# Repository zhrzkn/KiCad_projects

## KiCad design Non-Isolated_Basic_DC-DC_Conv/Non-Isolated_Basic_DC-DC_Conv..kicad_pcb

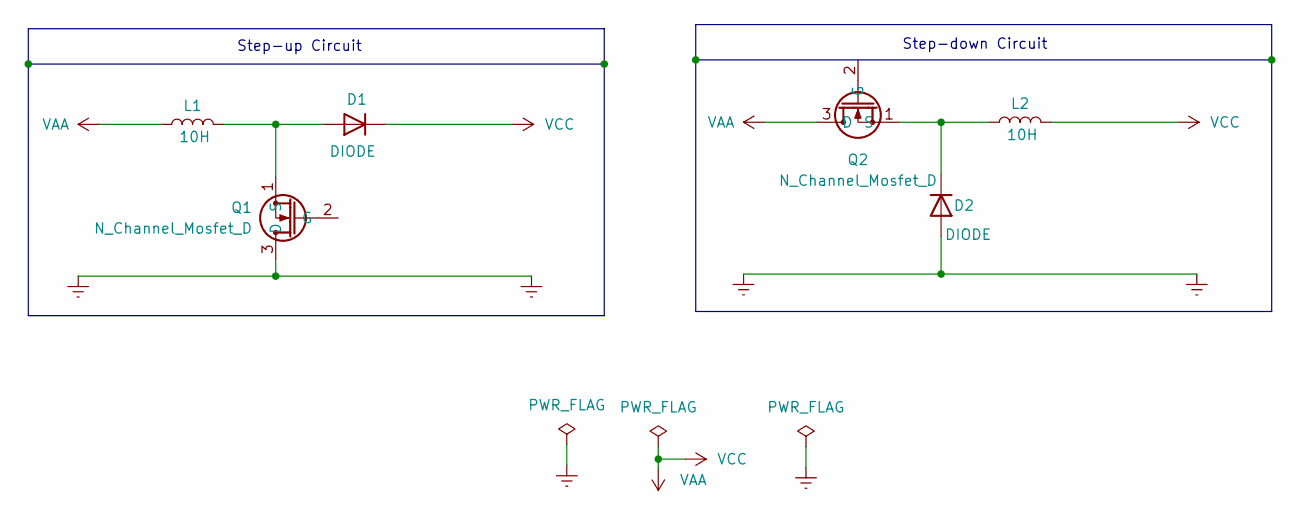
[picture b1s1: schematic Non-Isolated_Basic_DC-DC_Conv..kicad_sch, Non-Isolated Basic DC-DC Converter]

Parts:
D1, D2: DIODE; D_2010_5025Metric
L1, L2: 10H; L_0402_1005Metric
Q1, Q2: N_Channel_Mosfet_D; SOT-23

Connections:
Earth: D2.1 (A), Q1.3 (D)
unnamed: D1.1 (A), L1.2, Q1.1 (S)
unnamed: D2.2 (K), L2.1, Q2.1 (S)
VAA: D1.2 (K), L1.1, L2.2, Q2.3 (D)

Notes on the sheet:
Step-down Circuit
Step-up Circuit

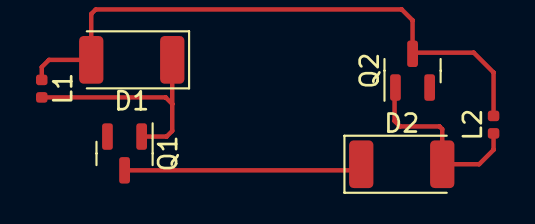
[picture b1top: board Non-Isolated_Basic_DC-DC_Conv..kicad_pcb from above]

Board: 2 copper layers, 6 parts (0 on the bottom side), 4 nets.

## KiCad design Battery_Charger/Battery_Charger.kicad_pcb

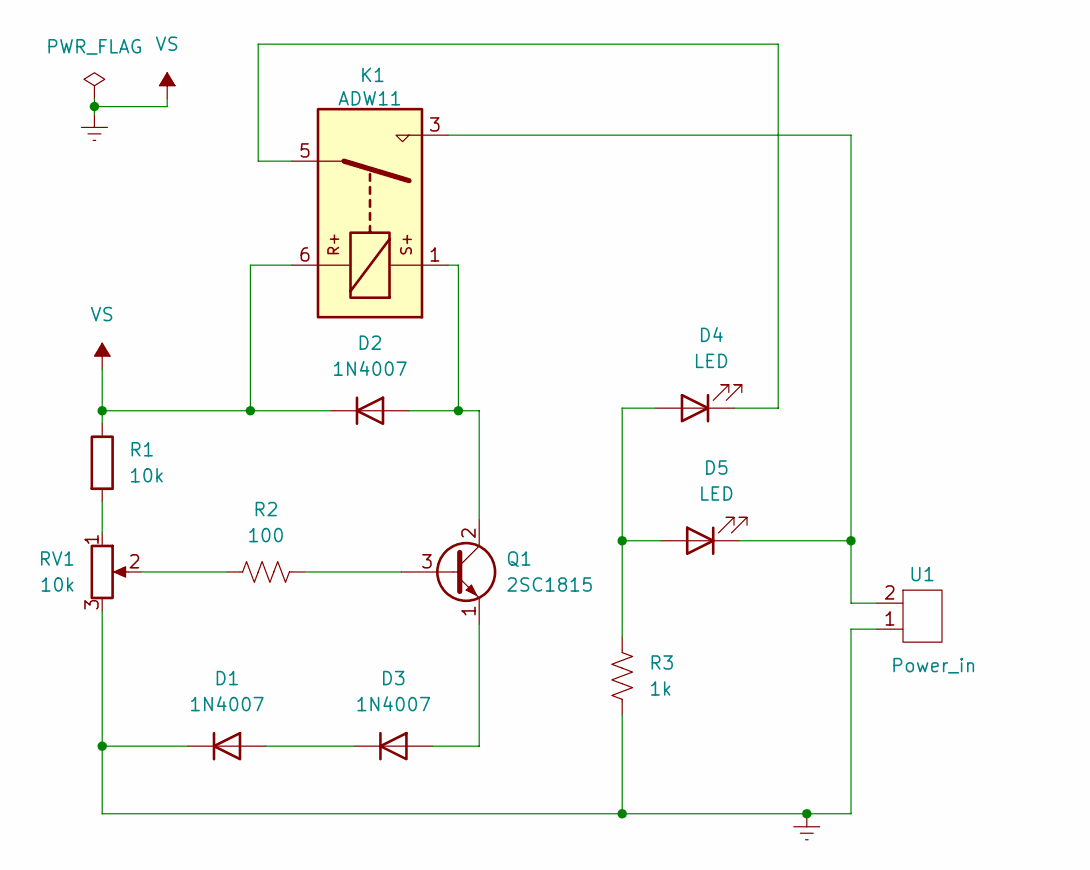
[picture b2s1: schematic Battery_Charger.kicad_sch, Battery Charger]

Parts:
D1, D2, D3: 1N4007; D_DO-41_SOD81_P10.16mm_Horizontal
D4, D5: LED; LED_D3.0mm_FlatTop
K1: ADW11; Relay_1P1T_NO_10x24x18.8mm_Panasonic_ADW11xxxxW_THT
Q1: 2SC1815; TO-92_Inline
R1: 10k; R_0805_2012Metric_Pad1.20x1.40mm_HandSolder
R2: 100; R_0805_2012Metric_Pad1.20x1.40mm_HandSolder
R3: 1k; R_0805_2012Metric_Pad1.20x1.40mm_HandSolder
RV1: 10k; Potentiometer_Bourns_3224J_Horizontal
U1: Power_in; TerminalBlock_bornier-2_P5.08mm

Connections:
Earth: D1.1 (K), D2.1 (K), K1.6, R1.1, R3.2, RV1.3, U1.1
unnamed: D1.2 (A), D3.1 (K)
unnamed: D2.2 (A), K1.1, Q1.2 (C)
unnamed: D3.2 (A), Q1.1 (E)
unnamed: D4.1 (K), K1.5
unnamed: D4.2 (A), D5.2 (A), R3.1
unnamed: D5.1 (K), K1.3, U1.2
unnamed: Q1.3 (B), R2.1
unnamed: R1.2, RV1.1
unnamed: R2.2, RV1.2

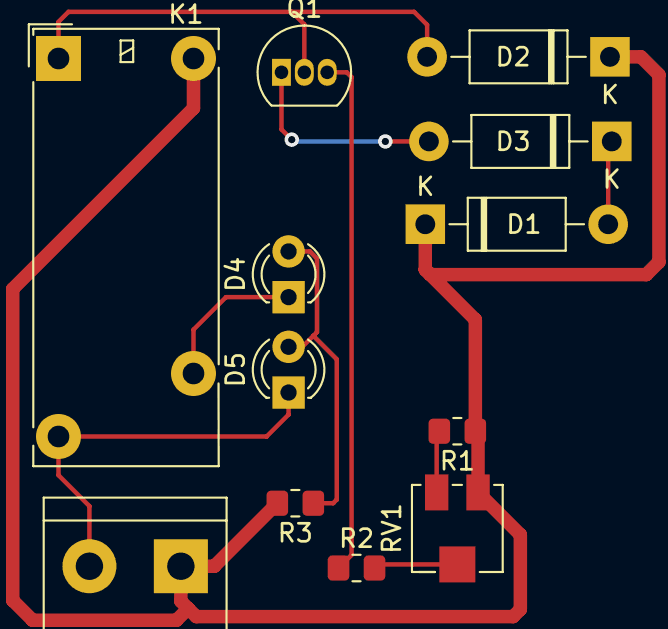
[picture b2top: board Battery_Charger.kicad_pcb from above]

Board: 2 copper layers, 12 parts (0 on the bottom side), 10 nets.

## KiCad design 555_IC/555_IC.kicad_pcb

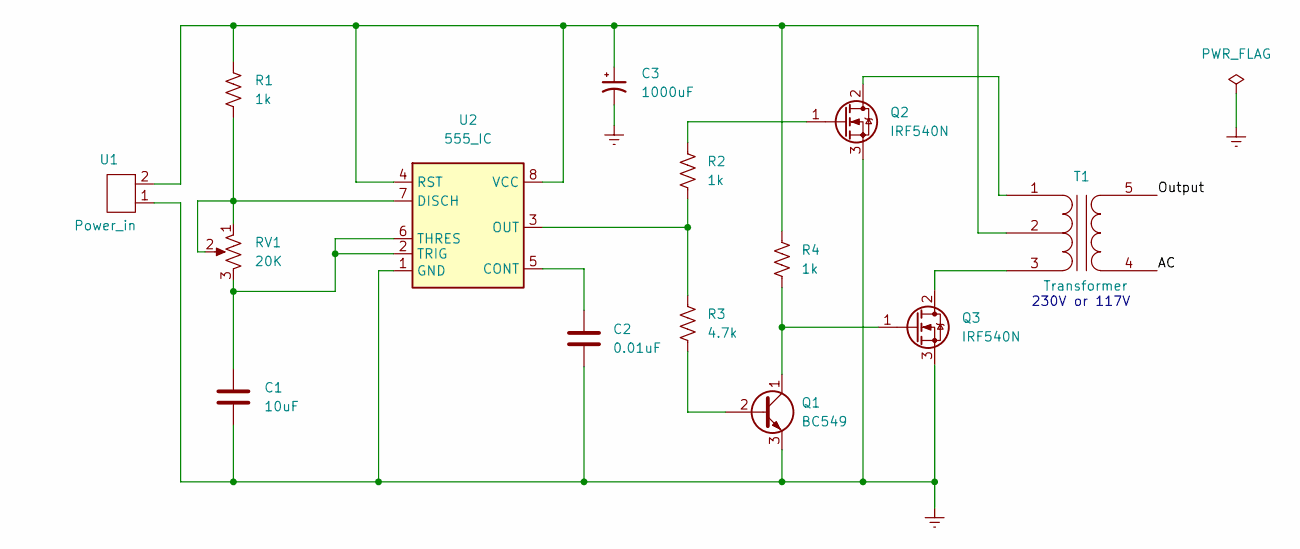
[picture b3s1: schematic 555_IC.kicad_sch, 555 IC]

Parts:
C1: 10uF; C_Disc_D4.7mm_W2.5mm_P5.00mm
C2: 0.01uF; CP_Radial_D10.0mm_P3.50mm
C3: 1000uF; C_Disc_D4.7mm_W2.5mm_P5.00mm
Q1: BC549; TO-92_Inline
Q2, Q3: IRF540N; TO-220-3_Vertical
R1, R2, R4: 1k; R_Axial_DIN0204_L3.6mm_D1.6mm_P5.08mm_Horizontal
R3: 4.7k; R_Axial_DIN0204_L3.6mm_D1.6mm_P5.08mm_Horizontal
RV1: 20K; Potentiometer_ACP_CA14-H4_Horizontal
T1: Transformer; Transformer_Toroid_Tapped_Horizontal_D10.5mm_Amidon-T37
U1: Power_in; TerminalBlock_bornier-2_P5.08mm
U2: 555_IC; LM358

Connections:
/AC: T1.4 (S1)
/Output: T1.5 (S2)
Earth: C1.2, C2.2, C3.2, Q1.3 (E), Q2.3 (S), Q3.3 (S), U1.1, U2.1 (GND)
unnamed: C1.1, RV1.3, U2.2 (TRIG), U2.6 (THRES)
unnamed: C2.1, U2.5 (CONT)
unnamed: C3.1, R1.1, R4.1, T1.2 (PM), U1.2, U2.4 (RST), U2.8 (VCC)
unnamed: Q1.1 (C), Q3.1 (G), R4.2
unnamed: Q1.2 (B), R3.2
unnamed: Q2.1 (G), R2.1
unnamed: Q2.2 (D), T1.1 (PR1)
unnamed: Q3.2 (D), T1.3 (PR2)
unnamed: R1.2, RV1.1, RV1.2, U2.7 (DISCH)
unnamed: R2.2, R3.1, U2.3 (OUT)

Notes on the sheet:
230V or 117V

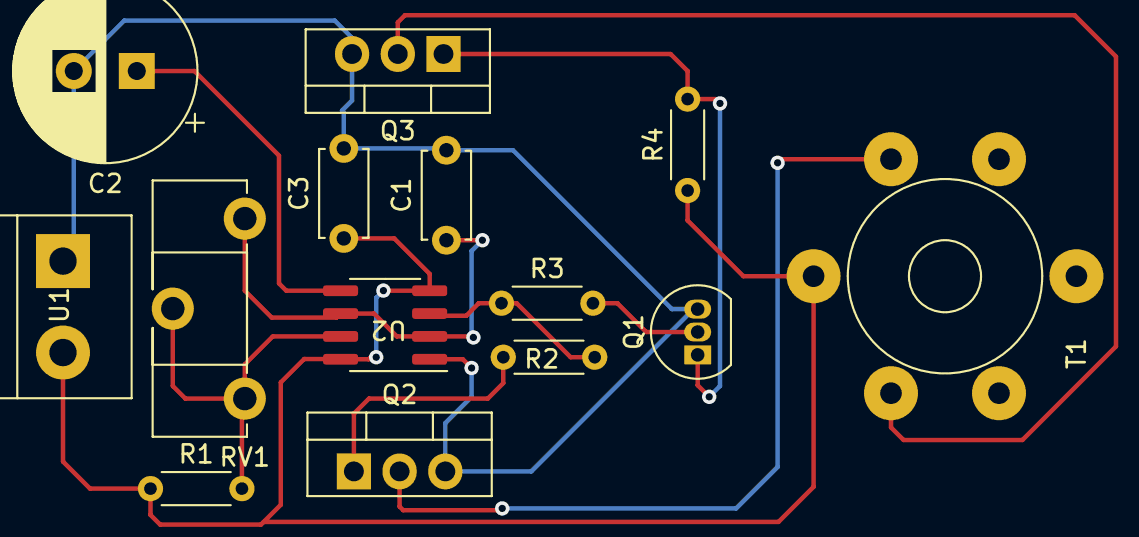
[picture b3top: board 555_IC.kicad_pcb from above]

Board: 2 copper layers, 14 parts (0 on the bottom side), 11 nets.

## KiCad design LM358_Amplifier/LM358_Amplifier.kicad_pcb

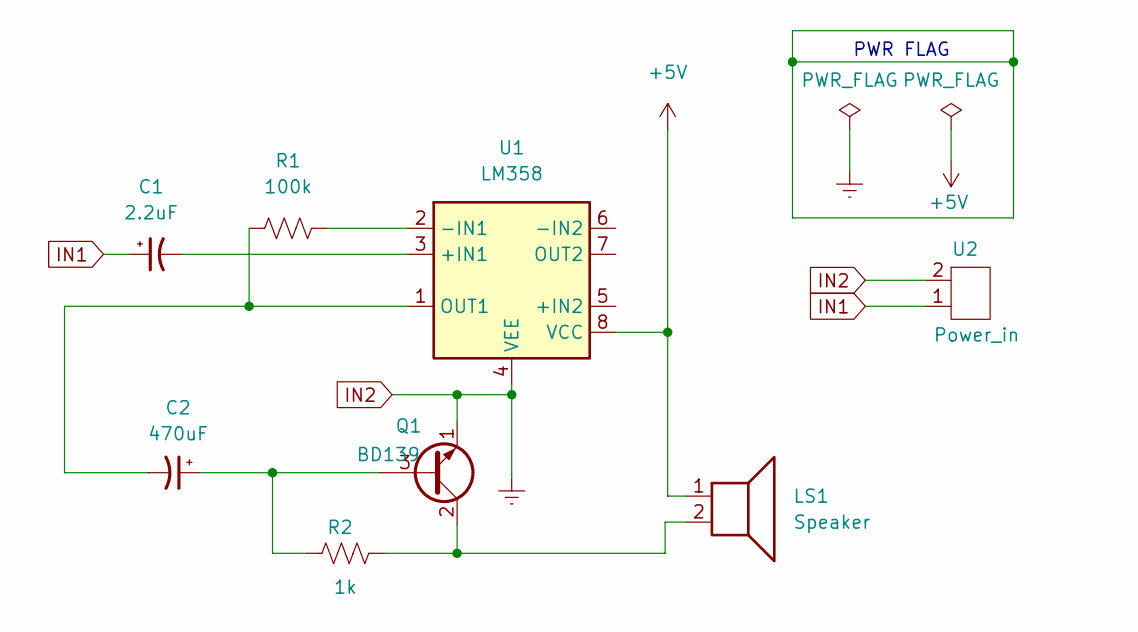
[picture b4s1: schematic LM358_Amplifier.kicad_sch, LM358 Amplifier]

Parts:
C1: 2.2uF; CP_Radial_D7.5mm_P2.50mm
C2: 470uF; CP_Radial_D8.0mm_P5.00mm
LS1: Speaker; Buzzer_15x7.5RM7.6
Q1: BD139; TO-126-3_Vertical
R1: 100k; R_Axial_DIN0204_L3.6mm_D1.6mm_P5.08mm_Horizontal
R2: 1k; R_Axial_DIN0204_L3.6mm_D1.6mm_P2.54mm_Vertical
U1: LM358
U2: Power_in; TerminalBlock_bornier-2_P5.08mm

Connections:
+5V: LS1.1, U1.8 (VCC)
IN1: C1.1, U2.1
IN2: Q1.1 (E), U1.4 (VEE), U2.2
unnamed: C1.2, U1.3 (+IN1)
unnamed: C2.1, Q1.3 (B), R2.1
unnamed: C2.2, R1.1, U1.1 (OUT1)
unnamed: LS1.2, Q1.2 (C), R2.2
unnamed: R1.2, U1.2 (-IN1)

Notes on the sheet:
PWR FLAG

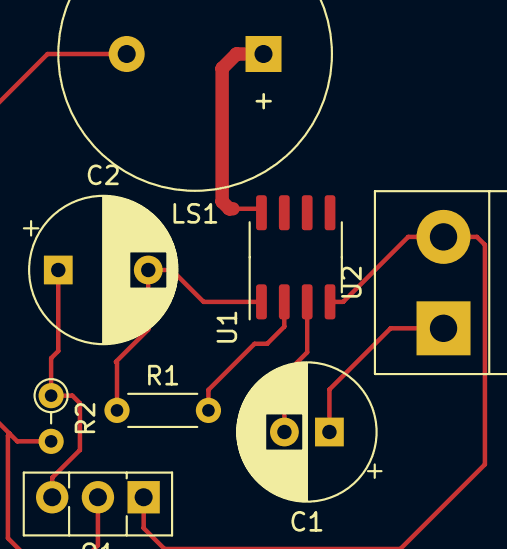
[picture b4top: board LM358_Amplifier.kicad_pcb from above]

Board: 2 copper layers, 8 parts (0 on the bottom side), 8 nets.

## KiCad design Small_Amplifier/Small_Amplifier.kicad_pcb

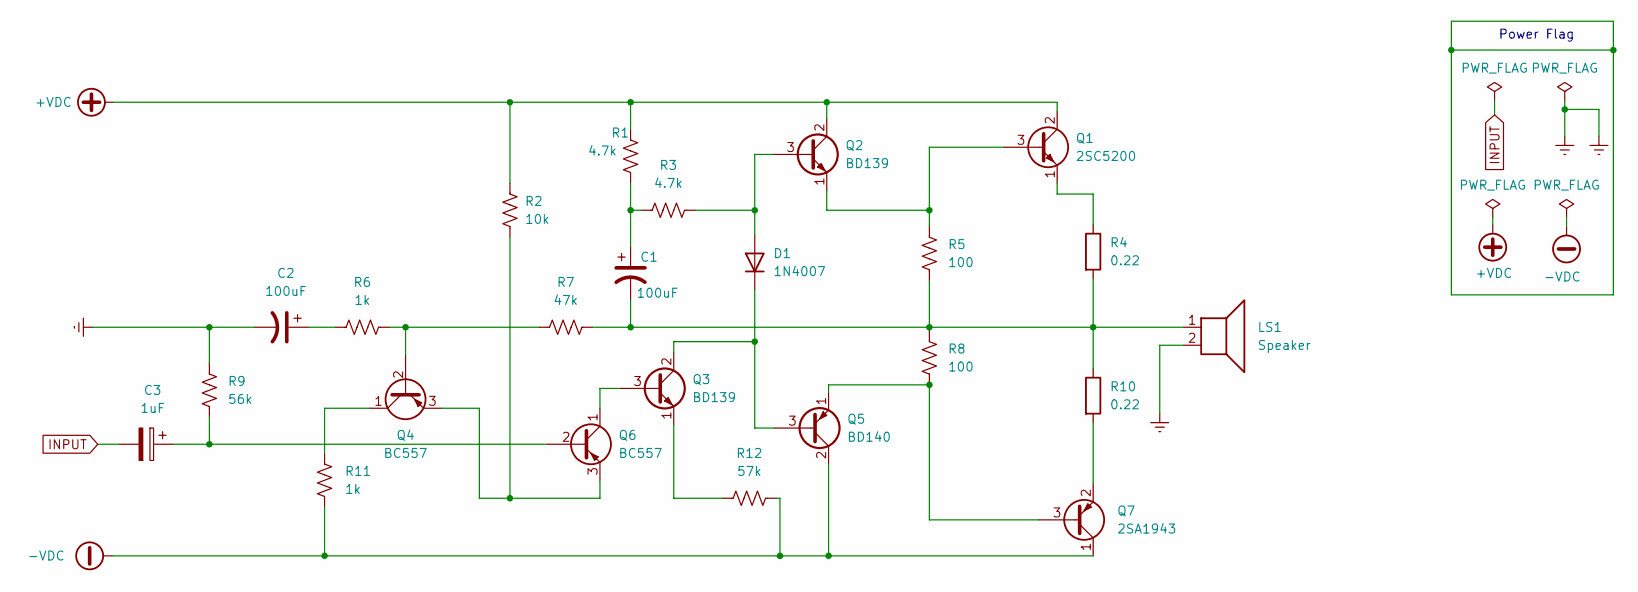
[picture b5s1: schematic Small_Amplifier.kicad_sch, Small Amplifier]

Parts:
C1, C2: 100uF; C_Radial_D6.3mm_H11.0mm_P2.50mm
C3: 1uF; C_Radial_D6.3mm_H11.0mm_P2.50mm
D1: 1N4007; D_DO-41_SOD81_P10.16mm_Horizontal
LS1: Speaker; Buzzer_15x7.5RM7.6
Q1: 2SC5200; TO-92_Inline
Q2, Q3: BD139; TO-126-3_Vertical
Q4: BC557; TO-92_Inline
Q5: BD140; TO-126-3_Vertical
Q6: BC557; TO-126-3_Vertical
Q7: 2SA1943; TO-92_Inline
R1, R3: 4.7k; R_Axial_DIN0204_L3.6mm_D1.6mm_P1.90mm_Vertical
R2: 10k; R_Axial_DIN0204_L3.6mm_D1.6mm_P1.90mm_Vertical
R4, R10: 0.22; R_Axial_DIN0204_L3.6mm_D1.6mm_P1.90mm_Vertical
R5, R8: 100; R_Axial_DIN0204_L3.6mm_D1.6mm_P1.90mm_Vertical
R6, R11: 1k; R_Axial_DIN0204_L3.6mm_D1.6mm_P1.90mm_Vertical
R7: 47k; R_Axial_DIN0204_L3.6mm_D1.6mm_P1.90mm_Vertical
R9: 56k; R_Axial_DIN0617_L17.0mm_D6.0mm_P7.62mm_Vertical
R12: 57k; R_Axial_DIN0617_L17.0mm_D6.0mm_P7.62mm_Vertical

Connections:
+VDC: Q1.2, Q2.2 (C), R1.1, R2.1
-VDC: Q5.2 (C), Q7.1, R11.2, R12.2
Earth: C2.2, LS1.2, R9.1
INPUT: C3.2
unnamed: C1.1, R1.2, R3.1
unnamed: C1.2, LS1.1, R4.2, R5.2, R7.2, R8.1, R10.1
unnamed: C2.1, R6.1
unnamed: C3.1, Q6.2 (B), R9.2
unnamed: D1.1 (K), Q3.2 (C), Q5.3 (B)
unnamed: D1.2 (A), Q2.3 (B), R3.2
unnamed: Q1.1, R4.1
unnamed: Q1.3, Q2.1 (E), R5.1
unnamed: Q3.1 (E), R12.1
unnamed: Q3.3 (B), Q6.1 (C)
unnamed: Q4.1 (C), R11.1
unnamed: Q4.2 (B), R6.2, R7.1
unnamed: Q4.3 (E), Q6.3 (E), R2.2
unnamed: Q5.1 (E), Q7.3, R8.2
unnamed: Q7.2, R10.2

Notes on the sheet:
Power Flag

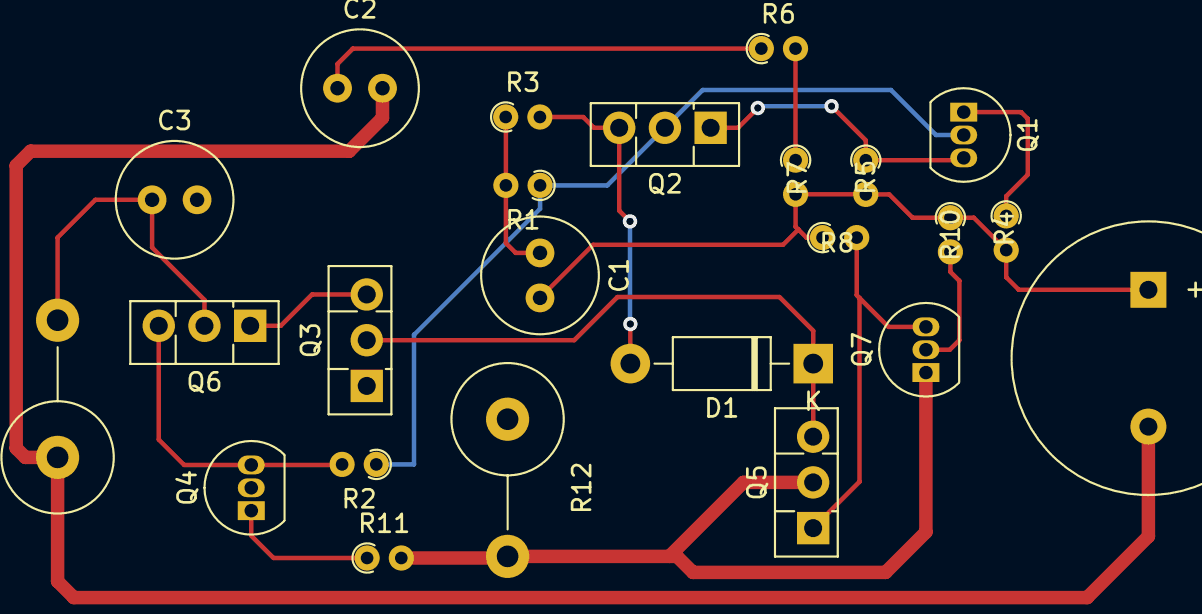
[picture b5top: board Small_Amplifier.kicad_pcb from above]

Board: 2 copper layers, 24 parts (0 on the bottom side), 18 nets.

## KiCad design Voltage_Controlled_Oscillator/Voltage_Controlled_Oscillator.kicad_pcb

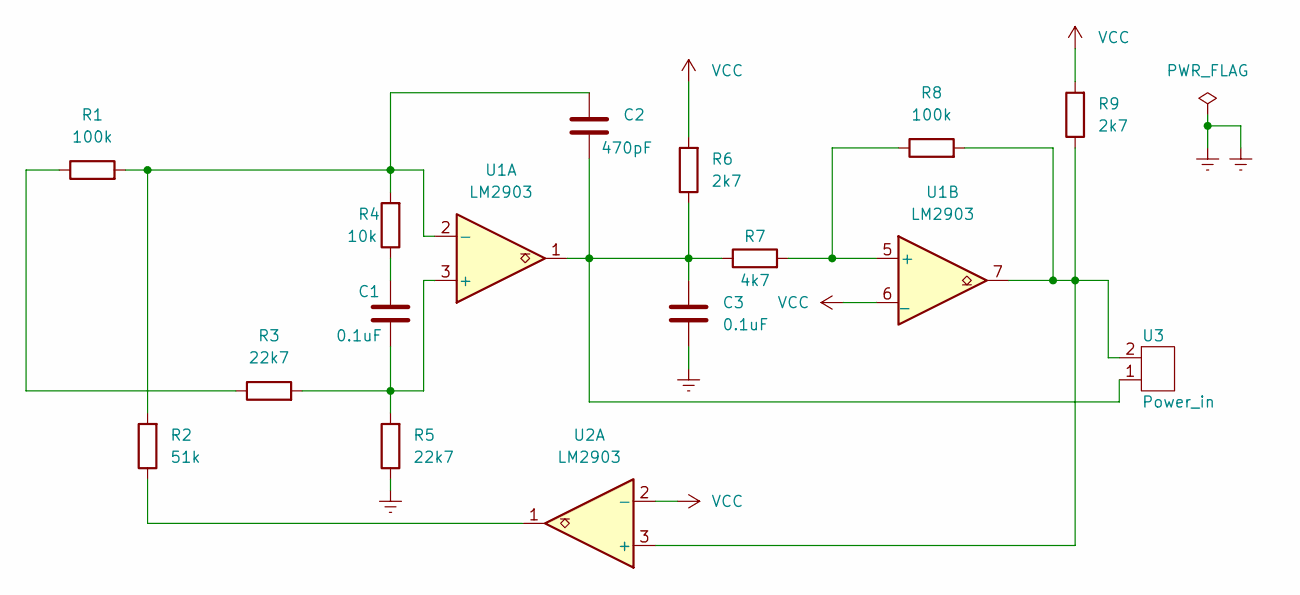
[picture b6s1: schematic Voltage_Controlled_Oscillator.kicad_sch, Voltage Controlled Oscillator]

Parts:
C1, C3: 0.1uF; C_Disc_D3.0mm_W1.6mm_P2.50mm
C2: 470pF; C_Disc_D3.0mm_W1.6mm_P2.50mm
R1, R8: 100k; R_Axial_DIN0204_L3.6mm_D1.6mm_P5.08mm_Horizontal
R2: 51k; R_Axial_DIN0204_L3.6mm_D1.6mm_P5.08mm_Horizontal
R3, R5: 22k7; R_Axial_DIN0204_L3.6mm_D1.6mm_P5.08mm_Horizontal
R4: 10k; R_Axial_DIN0204_L3.6mm_D1.6mm_P5.08mm_Horizontal
R6, R9: 2k7; R_Axial_DIN0204_L3.6mm_D1.6mm_P5.08mm_Horizontal
R7: 4k7; R_Axial_DIN0204_L3.6mm_D1.6mm_P5.08mm_Horizontal
U1, U2: LM2903; SOIC-8-1EP_3.9x4.9mm_P1.27mm_EP2.29x3mm
U3: Power_in; TerminalBlock_bornier-2_P5.08mm

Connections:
Earth: C3.2, R5.1
unnamed: C1.1, R4.1
unnamed: C1.2, R3.2, R5.2, U1.3 (+)
unnamed: C2.1, R1.2, R2.2, R4.2, U1.2 (-)
unnamed: C2.2, C3.1, R6.1, R7.1, U1.1, U3.1
unnamed: R1.1, R3.1
unnamed: R2.1, U2.1
unnamed: R7.2, R8.1, U1.5 (+)
unnamed: R8.2, R9.1, U1.7, U2.3 (+), U3.2
VCC: R6.2, R9.2, U1.6 (_), U2.2 (-)

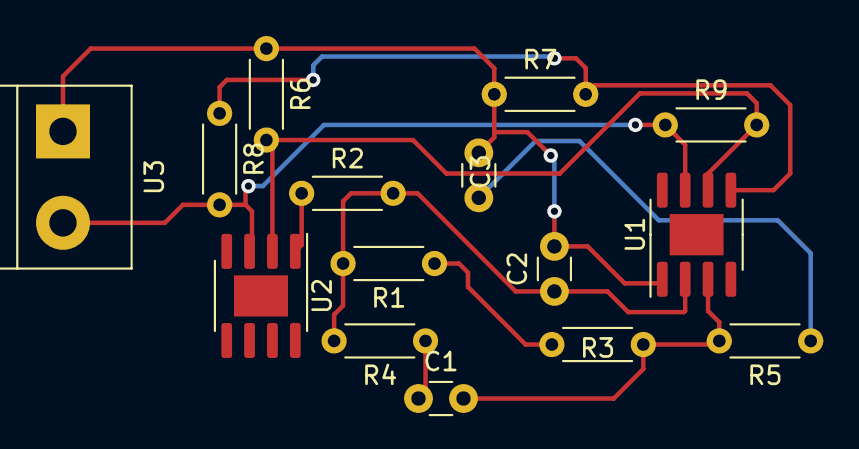
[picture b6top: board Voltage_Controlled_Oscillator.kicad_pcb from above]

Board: 2 copper layers, 15 parts (0 on the bottom side), 10 nets.

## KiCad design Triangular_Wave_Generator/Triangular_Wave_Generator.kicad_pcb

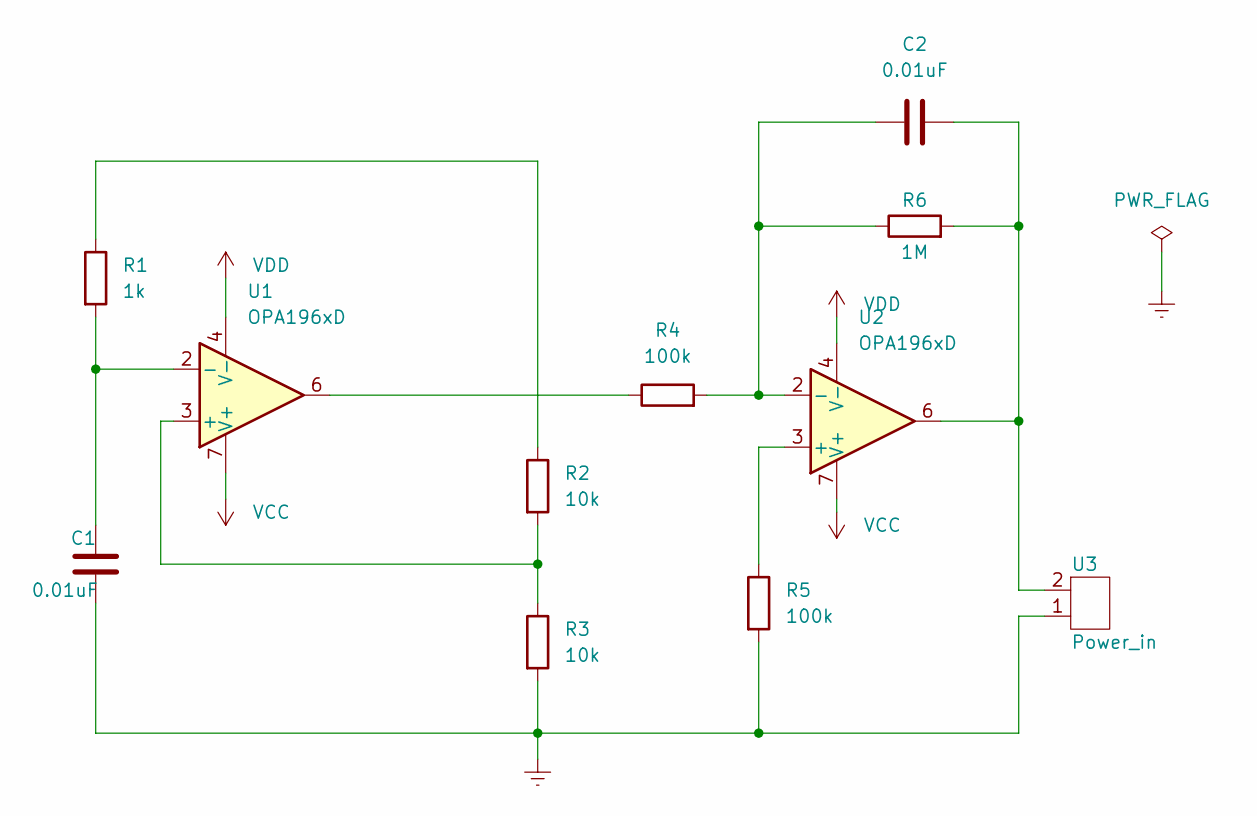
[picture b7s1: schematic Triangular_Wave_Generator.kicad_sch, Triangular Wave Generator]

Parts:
C1, C2: 0.01uF; C_0805_2012Metric
R1: 1k; R_0805_2012Metric
R2, R3: 10k; R_0805_2012Metric
R4, R5: 100k; R_0805_2012Metric
R6: 1M; R_0805_2012Metric
U1, U2: OPA196xD; SOIC-8_3.9x4.9mm_P1.27mm
U3: Power_in; TerminalBlock_bornier-2_P5.08mm

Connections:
Earth: C1.2, R3.2, R5.2, U3.1
unnamed: C1.1, R1.2, U1.2 (-)
unnamed: C2.1, R4.2, R6.1, U2.2 (-)
unnamed: C2.2, R6.2, U2.6, U3.2
unnamed: R1.1, R2.1
unnamed: R2.2, R3.1, U1.3 (+)
unnamed: R4.1, U1.6
unnamed: R5.1, U2.3 (+)
VCC: U1.7 (V+), U2.7 (V+)
VDD: U1.4 (V-), U2.4 (V-)

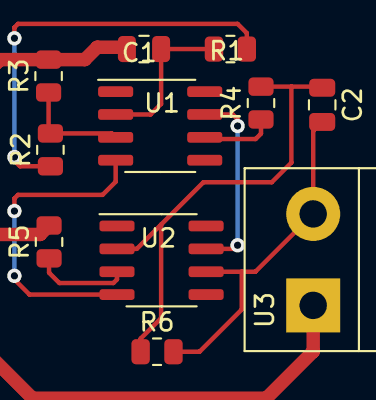
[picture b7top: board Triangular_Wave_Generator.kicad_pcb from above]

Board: 2 copper layers, 11 parts (0 on the bottom side), 10 nets.

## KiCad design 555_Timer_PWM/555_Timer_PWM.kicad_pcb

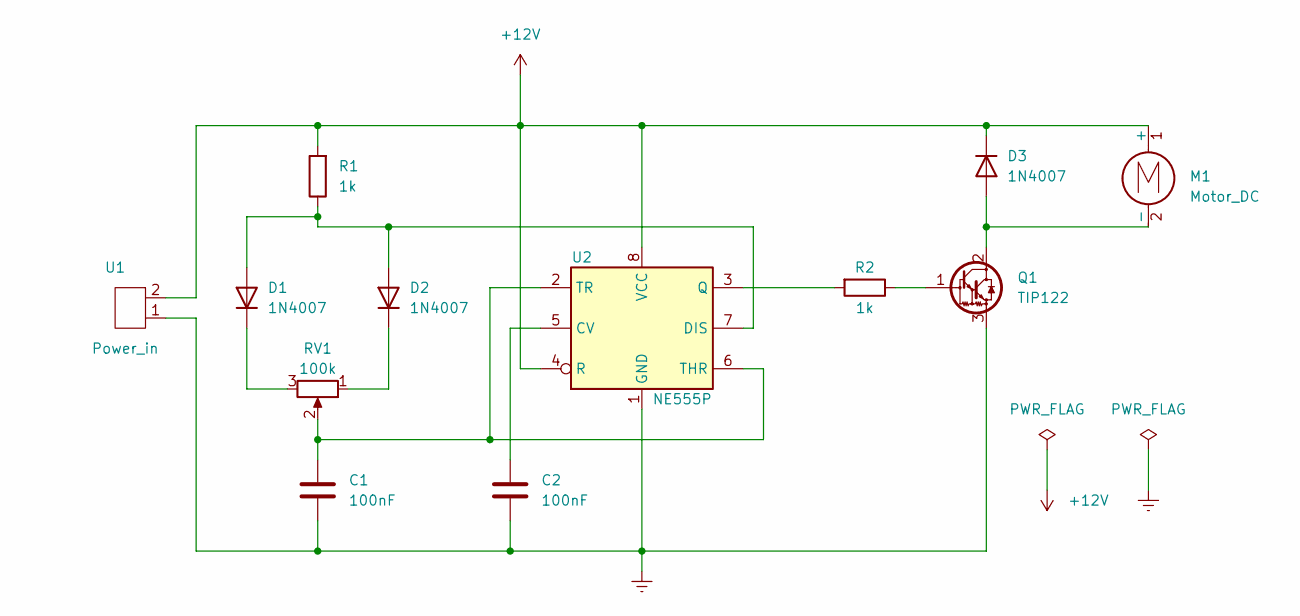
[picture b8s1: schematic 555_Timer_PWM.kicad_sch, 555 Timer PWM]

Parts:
C1, C2: 100nF; C_Disc_D3.0mm_W1.6mm_P2.50mm
D1, D2, D3: 1N4007; D_DO-41_SOD81_P10.16mm_Horizontal
M1: Motor_DC; TerminalBlock_bornier-2_P5.08mm
Q1: TIP122; TO-220-3_Vertical
R1, R2: 1k; R_Axial_DIN0204_L3.6mm_D1.6mm_P5.08mm_Horizontal
RV1: 100k; Potentiometer_ACP_CA9-V10_Vertical_Hole
U1: Power_in; TerminalBlock_bornier-2_P5.08mm
U2: NE555P; DIP-8_W7.62mm

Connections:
+12V: D3.1 (K), M1.1 (+), R1.2, U1.2, U2.4 (R), U2.8 (VCC)
Earth: C1.2, C2.2, Q1.3 (E), U1.1, U2.1 (GND)
unnamed: C1.1, RV1.2, U2.2 (TR), U2.6 (THR)
unnamed: C2.1, U2.5 (CV)
unnamed: D1.1 (K), RV1.3
unnamed: D2.1 (K), RV1.1
unnamed: D1.2 (A), D2.2 (A), R1.1, U2.7 (DIS)
unnamed: D3.2 (A), M1.2 (-), Q1.2 (C)
unnamed: Q1.1 (B), R2.1
unnamed: R2.2, U2.3 (Q)

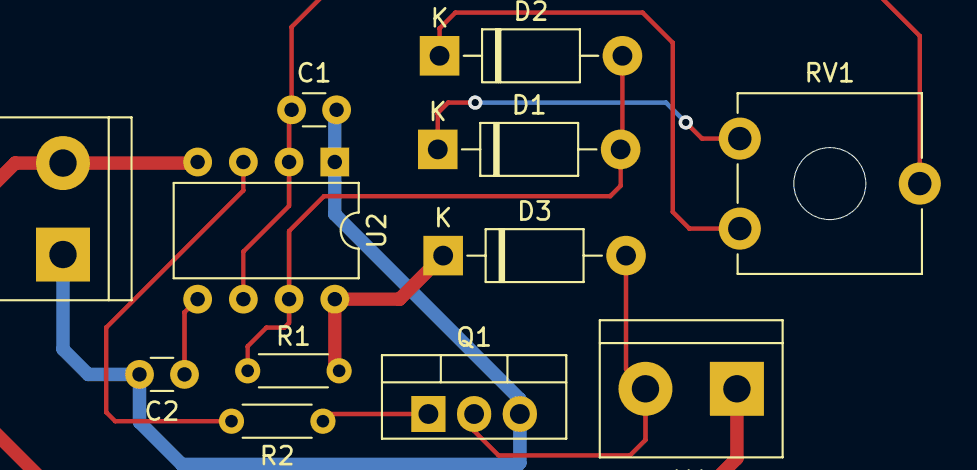
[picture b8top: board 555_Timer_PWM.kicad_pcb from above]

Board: 2 copper layers, 12 parts (0 on the bottom side), 10 nets.
